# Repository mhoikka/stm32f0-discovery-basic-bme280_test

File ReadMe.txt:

How to use this project:
-Fabricate a PCB using the Gerber and Drill files in the FabricationFiles folder
-Buy all components in the Components/AllComponents.csv file (breakout boards can be used for the NRF24L01+ and BME280 chips if soldering skills and access to a hot air gun are limiting factors. There is no need to solder on any of the components attached to the NRF and BME if the breakout boards are used.)
-Solder on all components according to the KiCAD schematic
-Run raspberry pi code in linked GitHub repo (https://github.com/mhoikka/SPItoNRF.git)
-Insert 2 CR2032 batteries to power on the device
-Collect data and modify code as needed

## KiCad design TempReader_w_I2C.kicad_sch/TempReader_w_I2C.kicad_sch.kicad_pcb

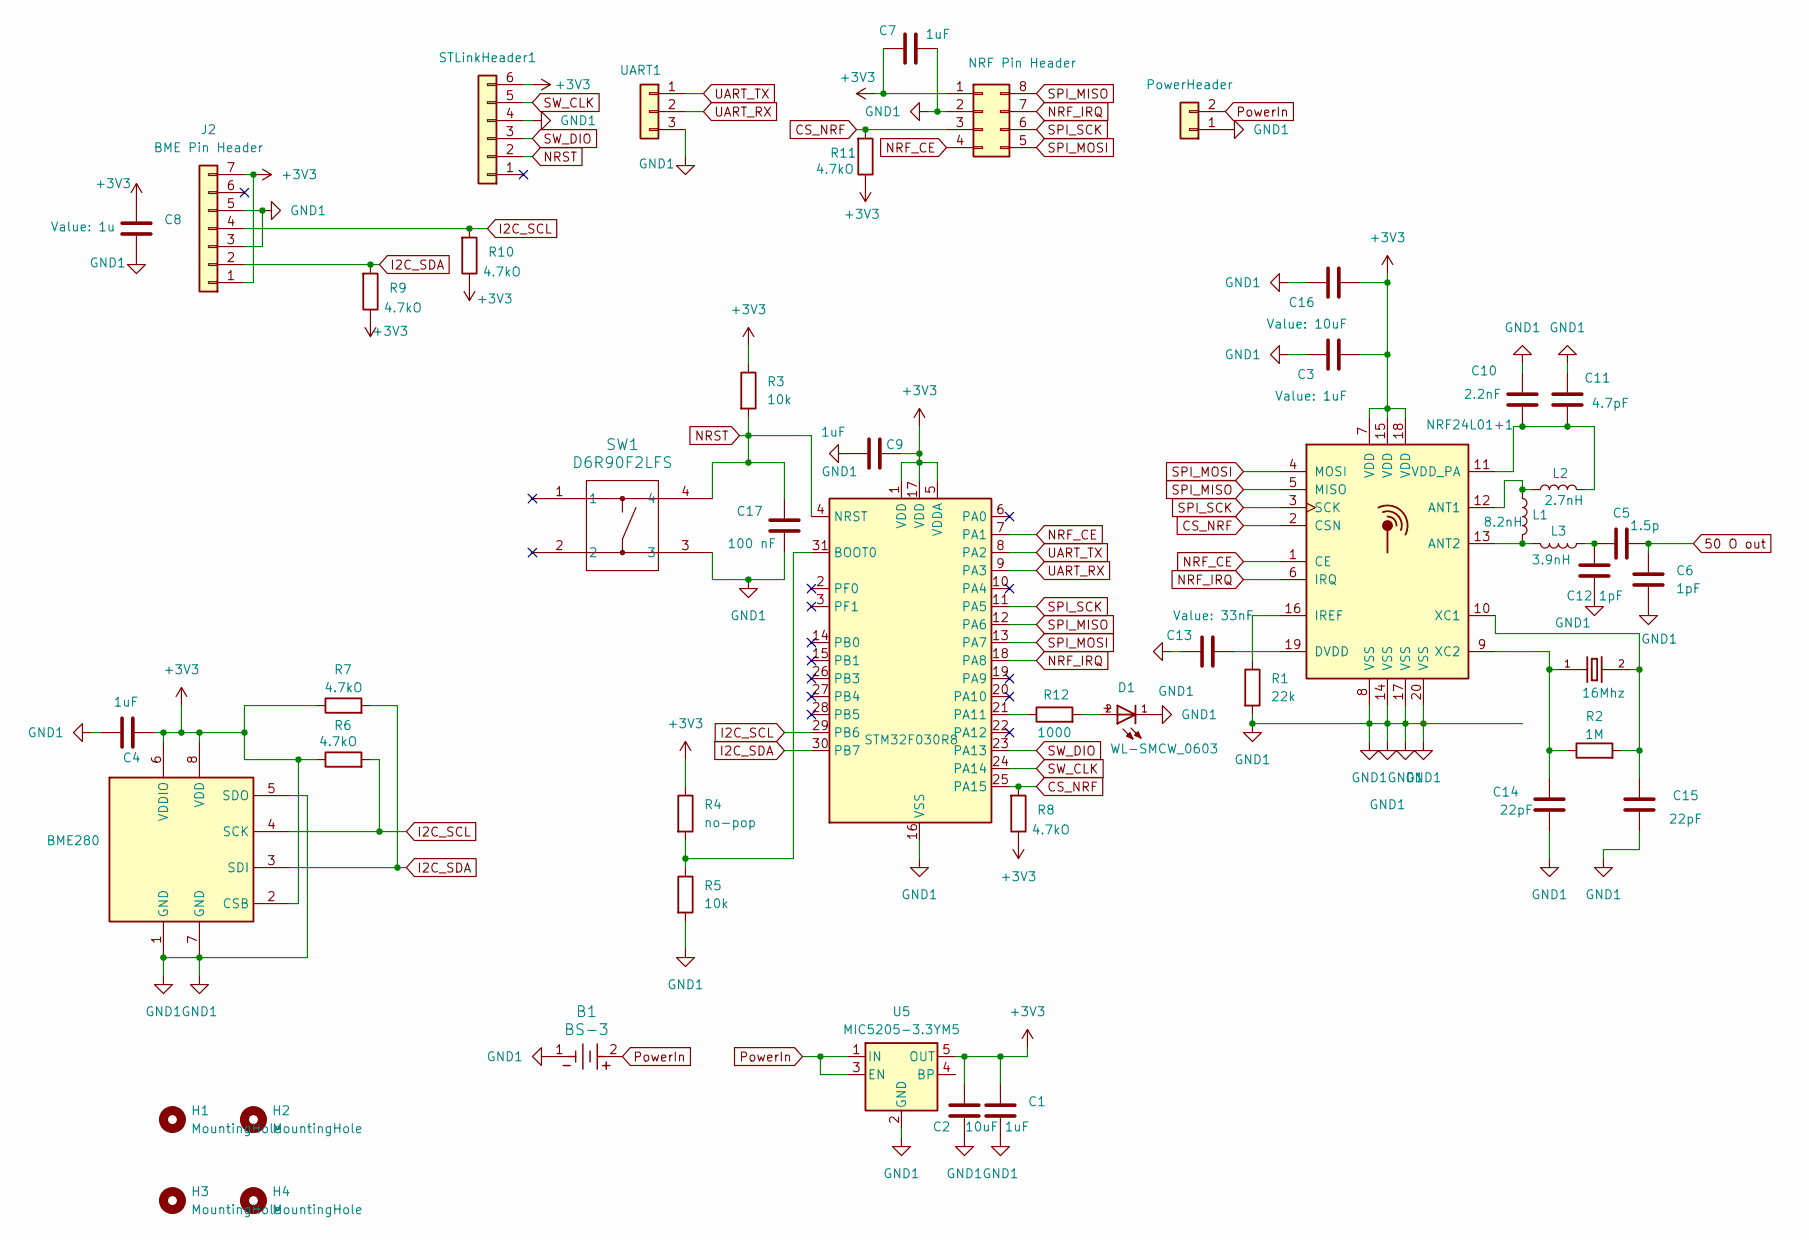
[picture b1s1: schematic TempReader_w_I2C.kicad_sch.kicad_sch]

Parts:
B1: BS-3; BS-3_MPD
BME280: BME280; Bosch_LGA-8_2.5x2.5mm_P0.65mm_ClockwisePinNumbering
C1, C3, C4, C7, C9: 1uF; C_0603_1608Metric_Pad1.08x0.95mm_HandSolder
C2, C16: 10uF; C_0603_1608Metric_Pad1.08x0.95mm_HandSolder
C5: 1.5p; C_0402_1005Metric_Pad0.74x0.62mm_HandSolder
C6, C12: 1pF; C_0402_1005Metric_Pad0.74x0.62mm_HandSolder
C8: 1u; C_0603_1608Metric_Pad1.08x0.95mm_HandSolder
C10: 2.2nF; C_0402_1005Metric_Pad0.74x0.62mm_HandSolder
C11: 4.7pF; C_0402_1005Metric_Pad0.74x0.62mm_HandSolder
C13: 33nF; C_0603_1608Metric_Pad1.08x0.95mm_HandSolder
C14, C15: 22pF; C_0603_1608Metric_Pad1.08x0.95mm_HandSolder
C17: 100 nF; C_0603_1608Metric_Pad1.08x0.95mm_HandSolder
D1: WL-SMCW_0603
H1, H2, H3, H4: MountingHole; MountingHole_2.2mm_M2
J1: NRF Pin Header; CON8_2X4_TU_SSQ
J2: BME Pin Header; PinHeader_1x07_P2.54mm_Vertical
J3: PowerHeader; PinHeader_1x02_P2.54mm_Vertical
L1: 8.2nH; L_0402_1005Metric_Pad0.77x0.64mm_HandSolder
L2: 2.7nH; L_0402_1005Metric_Pad0.77x0.64mm_HandSolder
L3: 3.9nH; L_0402_1005Metric_Pad0.77x0.64mm_HandSolder
NRF24L01+1: QFN-20-1EP_4x4mm_P0.5mm_EP2.5x2.5mm
R1: 22k; R_0603_1608Metric_Pad0.98x0.95mm_HandSolder
R2: 1M; R_0603_1608Metric_Pad0.98x0.95mm_HandSolder
R3, R5: 10k; R_0603_1608Metric_Pad0.98x0.95mm_HandSolder
R4: no-pop; R_0603_1608Metric_Pad0.98x0.95mm_HandSolder
R6, R7, R8, R9, R10, R11: 4.7kO; R_0603_1608Metric_Pad0.98x0.95mm_HandSolder
R12: 1000; R_0603_1608Metric
STLinkHeader1: NOT SURE WHAT THIS IS; PinHeader_1x06_P2.54mm_Vertical
STM32F030R8: LQFP-32_7x7mm_P0.8mm
SW1: D6R90F2LFS; D6R90_CNK
U5: MIC5205-3.3YM5; SOT-23-5
UART1: UART; PinHeader_1x03_P2.54mm_Vertical
Y2: 16Mhz; XTAL_ECS-160-12-4X-GM

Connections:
50 O out: C5.2, C6.1
+3V3: BME280.2 (CSB), BME280.6 (VDDIO), BME280.8 (VDD), C1.1, C2.1, C3.2, C4.1, C7.2, C8.1, C9.1, C16.2, J1.1, J2.1, J2.7, NRF24L01+1.7 (VDD), NRF24L01+1.15 (VDD), NRF24L01+1.18 (VDD), R3.1, R4.1, R6.1, R7.1, R8.1, R9.1, R10.1, R11.1, STLinkHeader1.6, STM32F030R8.1 (VDD), STM32F030R8.5 (VDDA), STM32F030R8.17 (VDD), U5.5 (OUT)
CS_NRF: J1.3, NRF24L01+1.2 (CSN), R8.2, R11.2, STM32F030R8.25 (PA15)
GND1: B1.1, BME280.1 (GND), BME280.5 (SDO), BME280.7 (GND), C1.2, C2.2, C3.1, C4.2, C6.2, C7.1, C8.2, C9.2, C10.1, C11.1, C12.2, C13.1, C14.2, C15.2, C16.1, C17.2, D1.1, J1.2, J2.3, J2.5, J3.1, NRF24L01+1.8 (VSS), NRF24L01+1.14 (VSS), NRF24L01+1.17 (VSS), NRF24L01+1.20 (VSS), R1.2, R5.2, STLinkHeader1.4, STM32F030R8.16 (VSS), STM32F030R8.32 (VSS), SW1.3, U5.2 (GND), UART1.3
I2C_SCL: BME280.4 (SCK), J2.4, R6.2, R10.2, STM32F030R8.29 (PB6)
I2C_SDA: BME280.3 (SDI), J2.2, R7.2, R9.2, STM32F030R8.30 (PB7)
NRF_CE: J1.4, NRF24L01+1.1 (CE), STM32F030R8.7 (PA1)
NRF_IRQ: J1.7, NRF24L01+1.6 (IRQ), STM32F030R8.18 (PA8)
NRST: C17.1, R3.2, STLinkHeader1.2, STM32F030R8.4 (NRST), SW1.4
unnamed: C5.1, C12.1, L3.1
unnamed: D1.2, R12.2
unnamed: L1.1, L2.1, NRF24L01+1.12 (ANT1)
unnamed: L1.2, L3.2, NRF24L01+1.13 (ANT2)
unnamed: C13.2, NRF24L01+1.19 (DVDD)
unnamed: NRF24L01+1.16 (IREF), R1.1
unnamed: C10.2, C11.2, L2.2, NRF24L01+1.11 (VDD_PA)
unnamed: C15.1, NRF24L01+1.10 (XC1), R2.2, Y2.2
unnamed: C14.1, NRF24L01+1.9 (XC2), R2.1, Y2.1
unnamed: R4.2, R5.1, STM32F030R8.31 (BOOT0)
unnamed: R12.1, STM32F030R8.21 (PA11)
PowerIn: B1.2, J3.2, U5.1 (IN), U5.3 (EN)
SPI_MISO: J1.8, NRF24L01+1.5 (MISO), STM32F030R8.12 (PA6)
SPI_MOSI: J1.5, NRF24L01+1.4 (MOSI), STM32F030R8.13 (PA7)
SPI_SCK: J1.6, NRF24L01+1.3 (SCK), STM32F030R8.11 (PA5)
SW_CLK: STLinkHeader1.5, STM32F030R8.24 (PA14)
SW_DIO: STLinkHeader1.3, STM32F030R8.23 (PA13)
UART_RX: STM32F030R8.9 (PA3), UART1.2
UART_TX: STM32F030R8.8 (PA2), UART1.1

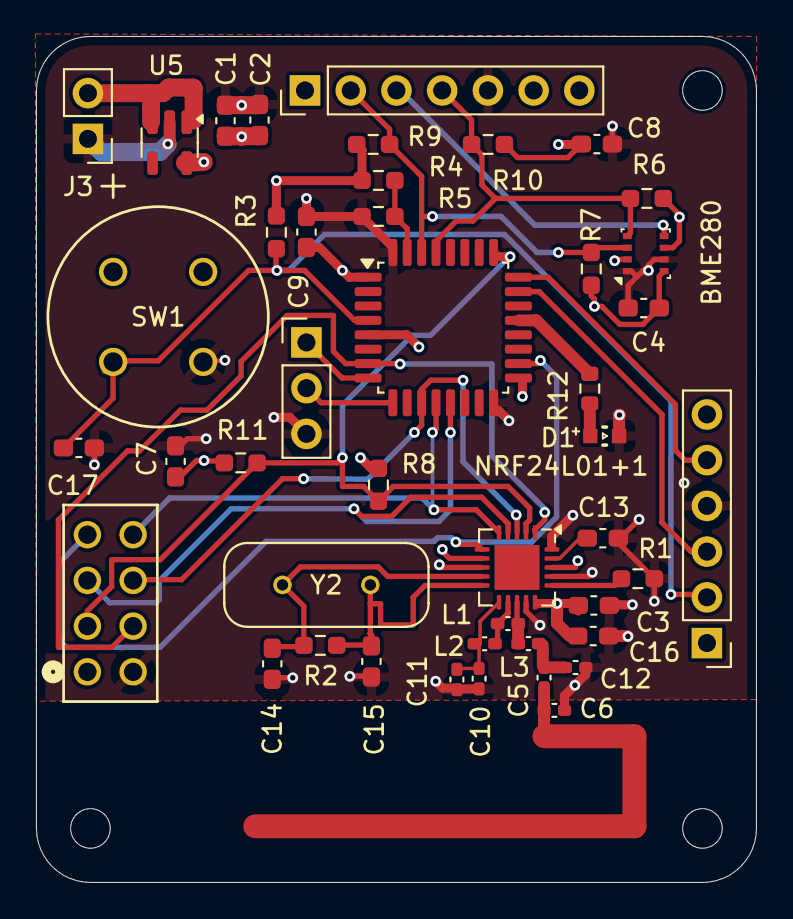
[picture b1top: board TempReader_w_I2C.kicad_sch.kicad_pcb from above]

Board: 4 copper layers, 40.0 x 47.0 mm, 47 parts (0 on the bottom side), 28 nets.

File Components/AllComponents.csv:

"Reference","Value","Datasheet","Footprint","Qty","DNP"
"B1","BS-3","BS-3","footprints:BS-3_MPD","1",""
"BME280","BME280","https://www.bosch-sensortec.com/media/boschsensortec/downloa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","Package_LGA:Bosch_LGA-8_2.5x2.5mm_P0.65mm_ClockwisePinNumbering","1",""
"C1,C3,C4,C7,C9","1uF","~","Capacitor_SMD:C_0603_1608Metric_Pad1.08x0.95mm_HandSolder","5",""
"C2,C16","10uF","~","Capacitor_SMD:C_0603_1608Metric_Pad1.08x0.95mm_HandSolder","2",""
"C5","1.5p","~","Capacitor_SMD:C_0402_1005Metric_Pad0.74x0.62mm_HandSolder","1",""
"C6,C12","1pF","~","Capacitor_SMD:C_0402_1005Metric_Pad0.74x0.62mm_HandSolder","2",""
"C8","1u","~","Capacitor_SMD:C_0603_1608Metric_Pad1.08x0.95mm_HandSolder","1",""
"C10","2.2nF","~","Capacitor_SMD:C_0402_1005Metric_Pad0.74x0.62mm_HandSolder","1",""
"C11","4.7pF","~","Capacitor_SMD:C_0402_1005Metric_Pad0.74x0.62mm_HandSolder","1",""
"C13","33nF","~","Capacitor_SMD:C_0603_1608Metric_Pad1.08x0.95mm_HandSolder","1",""
"C14,C15","22pF","~","Capacitor_SMD:C_0603_1608Metric_Pad1.08x0.95mm_HandSolder","2",""
"C17","100 nF","~","Capacitor_SMD:C_0603_1608Metric_Pad1.08x0.95mm_HandSolder","1",""
"D1","WL-SMCW_0603","","footprints:WL-SMCW_0603","1",""
"J1","NRF Pin Header","~","footprints:CON8_2X4_TU_SSQ","1",""
"J2","BME Pin Header","~","Connector_PinHeader_2.54mm:PinHeader_1x07_P2.54mm_Vertical","1",""
"J3","PowerHeader","~","Connector_PinHeader_2.54mm:PinHeader_1x02_P2.54mm_Vertical","1",""
"L1","8.2nH","~","Inductor_SMD:L_0402_1005Metric_Pad0.77x0.64mm_HandSolder","1",""
"L2","2.7nH","~","Inductor_SMD:L_0402_1005Metric_Pad0.77x0.64mm_HandSolder","1",""
"L3","3.9nH","~","Inductor_SMD:L_0402_1005Metric_Pad0.77x0.64mm_HandSolder","1",""
"NRF24L01+1,STM32F030R8","~","-- mixed values --","-- mixed values --","2",""
"R1","22k","~","Resistor_SMD:R_0603_1608Metric_Pad0.98x0.95mm_HandSolder","1",""
"R2","1M","~","Resistor_SMD:R_0603_1608Metric_Pad0.98x0.95mm_HandSolder","1",""
"R3,R5","10k","~","Resistor_SMD:R_0603_1608Metric_Pad0.98x0.95mm_HandSolder","2",""
"R4","no-pop","~","Resistor_SMD:R_0603_1608Metric_Pad0.98x0.95mm_HandSolder","1",""
"R6,R7,R8,R9,R10,R11","4.7kO","~","Resistor_SMD:R_0603_1608Metric_Pad0.98x0.95mm_HandSolder","6",""
"R12","1000","~","Resistor_SMD:R_0603_1608Metric","1",""
"STLinkHeader1","NOT SURE WHAT THIS IS","~","Connector_PinHeader_2.54mm:PinHeader_1x06_P2.54mm_Vertical","1",""
"SW1","D6R90F2LFS","D6R90F2LFS","D6R90_CNK","1",""
"U5","MIC5205-3.3YM5","http://ww1.microchip.com/downloads/en/DeviceDoc/20005785A.pdf","Package_TO_SOT_SMD:SOT-23-5","1",""
"UART1","UART","~","Connector_PinHeader_2.54mm:PinHeader_1x03_P2.54mm_Vertical","1",""
"Y2","16Mhz","","ECS-160-12-4X-GM:XTAL_ECS-160-12-4X-GM","1",""

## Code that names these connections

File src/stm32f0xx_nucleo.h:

/**
  ******************************************************************************
  * @file    stm32f0xx_nucleo.h
  * @author  MCD Application Team
  * @version V1.0.0
  * @date    11-February-2014
  * @brief   This file contains all the functions prototypes for the
  *          stm32f0xx_nucleo.c driver.
  ******************************************************************************
  * @attention
  *
  * <h2><center>&copy; COPYRIGHT 2014 STMicroelectronics</center></h2>
  *
  * Licensed under MCD-ST Liberty SW License Agreement V2, (the "License");
  * You may not use this file except in compliance with the License.
  * You may obtain a copy of the License at:
  *
  *        http://www.st.com/software_license_agreement_liberty_v2
  *
  * Unless required by applicable law or agreed to in writing, software 
  * distributed under the License is distributed on an "AS IS" BASIS, 
  * WITHOUT WARRANTIES OR CONDITIONS OF ANY KIND, either express or implied.
  * See the License for the specific language governing permissions and
  * limitations under the License.
  *
  ******************************************************************************
  */

/* Define to prevent recursive inclusion -------------------------------------*/
#ifndef __STM32F0XX_NUCLEO_H
#define __STM32F0XX_NUCLEO_H

#ifdef __cplusplus
 extern "C" {
#endif
                                              
/* Includes ------------------------------------------------------------------*/
#include "stm32f0xx.h"
#include "stm32f0xx_adc.h"

/** @addtogroup Utilities
  * @{
  */ 

/** @addtogroup STM32F0XX_NUCLEO
  * @{
  */
      
/** @defgroup STM32F0XX_NUCLEO_LOW_LEVEL 
  * @brief This file provides set of firmware functions to manage Leds and push-button
  *        available on STM32NUCLEO Kit from STMicroelectronics.
  * @{
  */

/** @defgroup STM32F0XX_NUCLEO_LOW_LEVEL_Exported_Types
  * @{
  */
typedef enum 
{
  LED2 = 0,
  
} Led_TypeDef;

typedef enum 
{  
  BUTTON_USER = 0,
} Button_TypeDef;

typedef enum 
{  
  BUTTON_MODE_GPIO = 0,
  BUTTON_MODE_EXTI = 1
} ButtonMode_TypeDef; 

/* The Joystick is available on adafruit 1.8" TFT shield */     
typedef enum 
{ 
  JOY_NONE = 0,
  JOY_SEL = 1,
  JOY_DOWN = 2,
  JOY_LEFT = 3,
  JOY_RIGHT = 4,
  JOY_UP = 5
} JOYState_TypeDef;

/**
  * @}
  */

/** @defgroup STM32F0XX_NUCLEO_LOW_LEVEL_Exported_Macros
  * @{
  */
/**
  * @brief LCD control lines (CS and DC) management
  */
#define LCD_CS_HIGH() LCD_CS_GPIO_PORT->BSRR = LCD_CS_PIN
#define LCD_CS_LOW()  LCD_CS_GPIO_PORT->BRR = LCD_CS_PIN
#define LCD_DC_HIGH() LCD_DC_GPIO_PORT->BSRR = LCD_DC_PIN
#define LCD_DC_LOW()  LCD_DC_GPIO_PORT->BRR = LCD_DC_PIN

/**
  * @brief SD CS line management 
  */
#define SD_CS_HIGH()  SD_CS_GPIO_PORT->BSRR = SD_CS_PIN
#define SD_CS_LOW()   SD_CS_GPIO_PORT->BRR = SD_CS_PIN    

/**
  * @}
  */  

/** @defgroup STM32F0xx_NUCLEO_LOW_LEVEL_Exported_Constants
  * @{
  */ 
/** @addtogroup STM32F0xx_NUCLEO_LOW_LEVEL_LED
  * @{
  */
#define LEDn                             1

#define LED2_PIN                         GPIO_Pin_5
#define LED2_GPIO_PORT                   GPIOA
#define LED2_GPIO_CLK                    RCC_AHBPeriph_GPIOA  

/**
  * @}
  */ 
/** @addtogroup STM32F0xx_NUCLEO_LOW_LEVEL_BUTTON
  * @{
  */  
#define BUTTONn                          1  

/**
 * @brief Wakeup push-button
 */
#define USER_BUTTON_PIN                GPIO_Pin_13
#define USER_BUTTON_GPIO_PORT          GPIOC
#define USER_BUTTON_GPIO_CLK           RCC_AHBPeriph_GPIOC
#define USER_BUTTON_EXTI_LINE          EXTI_Line13
#define USER_BUTTON_EXTI_PORT_SOURCE   EXTI_PortSourceGPIOC
#define USER_BUTTON_EXTI_PIN_SOURCE    EXTI_PinSource13
#define USER_BUTTON_EXTI_IRQn          EXTI4_15_IRQn 
/**
  * @}
  */
    
/** @addtogroup STM32F0XX_NUCLEO_LOW_LEVEL_SPI
  * @{
  */
/**
  * @brief  SPI Interface pins
  */
/* The LCD and uSD card are available on adafruit 1.8" TFT shield */
#define LCD_SD_SPI                    SPI1
#define LCD_SD_SPI_CLK                RCC_APB2Periph_SPI1

#define SPI_SCK_PIN                   GPIO_Pin_5                  /* PA.05 */
#define SPI_SCK_GPIO_PORT             GPIOA                       /* GPIOA */
#define SPI_SCK_GPIO_CLK              RCC_AHBPeriph_GPIOA
#define SPI_SCK_SOURCE                GPIO_PinSource5
#define SPI_SCK_AF                    GPIO_AF_0

#define SPI_MISO_PIN                  GPIO_Pin_6                  /* PA.06 */
#define SPI_MISO_GPIO_PORT            GPIOA                       /* GPIOA */
#define SPI_MISO_GPIO_CLK             RCC_AHBPeriph_GPIOA
#define SPI_MISO_SOURCE               GPIO_PinSource6
#define SPI_MISO_AF                   GPIO_AF_0

#define SPI_MOSI_PIN                  GPIO_Pin_7                  /* PA.07 */
#define SPI_MOSI_GPIO_PORT            GPIOA                       /* GPIOA */
#define SPI_MOSI_GPIO_CLK             RCC_AHBPeriph_GPIOA
#define SPI_MOSI_SOURCE               GPIO_PinSource7
#define SPI_MOSI_AF                   GPIO_AF_0
/**
  * @}
  */  
    
/**
  * @brief  SD Chip Select pin
  */
#define SD_CS_PIN                     GPIO_Pin_5                  /* PB.5 */
#define SD_CS_GPIO_PORT               GPIOB                       /* GPIOB */
#define SD_CS_GPIO_CLK                RCC_AHBPeriph_GPIOB

/**
  * @brief  LCD Data/Command pin
  */
#define LCD_DC_PIN                    GPIO_Pin_9                  /* PA.9 */
#define LCD_DC_GPIO_PORT              GPIOA                       /* GPIOA */
#define LCD_DC_GPIO_CLK               RCC_AHBPeriph_GPIOA

/**
  * @brief  LCD Chip Select pin
  */
#define LCD_CS_PIN                    GPIO_Pin_6                  /* PB.6*/
#define LCD_CS_GPIO_PORT              GPIOB                       /* GPIOB */
#define LCD_CS_GPIO_CLK               RCC_AHBPeriph_GPIOB
     
/**
  * @brief  ADC Interface pins
  */
/* The ADC is used to detect motion of Joystick available on adafruit 1.8" TFT shield */   
#define ADCx                            ADC1
#define ADC_CLK                         RCC_APB2Periph_ADC1
    
#define ADC_GPIO_PIN                    GPIO_Pin_0                  /* PB.0  */
#define ADC_GPIO_PORT                   GPIOB                       /* GPIOB */
#define ADC_GPIO_CLK                    RCC_AHBPeriph_GPIOB
/**
  * @}
  */

/** @defgroup STM32F0XX_NUCLEO_LOW_LEVEL_Exported_Functions
  * @{
  */
void STM_EVAL_LEDInit(Led_TypeDef Led);
void STM_EVAL_LEDOn(Led_TypeDef Led);
void STM_EVAL_LEDOff(Led_TypeDef Led);
void STM_EVAL_LEDToggle(Led_TypeDef Led);
void STM_EVAL_PBInit(Button_TypeDef Button, ButtonMode_TypeDef Button_Mode);
uint32_t STM_EVAL_PBGetState(Button_TypeDef Button);

/* Functions to configure and manage the STM32F0xx resources (SPI and ADC) used to drive 
   LCD, uSD card and Joystick available in adafruit 1.8" TFT shield */
void STM_SPI_Init(void);
uint8_t STM_SPI_WriteRead(uint8_t Data);
void LCD_CtrlLines_Config(void);
void SD_CtrlLines_Config(void);
void STM_ADC_Config(void);
JOYState_TypeDef STM_Get_JOYState(void);

/**
  * @}
  */

#ifdef __cplusplus
}
#endif

#endif /* __STM32F0XX_NUCLEO_H */
/**
  * @}
  */ 

/**
  * @}
  */ 

/**
  * @}
  */ 

/************************ (C) COPYRIGHT STMicroelectronics *****END OF FILE****/

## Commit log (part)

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2024-10-06 SPI test was not in fact working
2024-10-08 Please tell me this was not the issue
2024-10-08 This was probably the issue
2024-10-08 Try adding a delay
2024-10-08 Try adding a delay for powerup
2024-10-08 Wait for powerup to read
2024-10-09 New read/write SPI function
2024-10-10 Cleaning up code
2024-10-19 KiCAD files
2024-10-25 Added test code to transmit one byte of data
2024-10-25 Moved variable declarations
2024-10-25 Added debug lines
2024-10-26 Removed debug lines
2024-10-26 Fix array copy
2024-10-26 Fix array copy the sequel
2024-10-26 Add code to flush TX FIFO
2024-10-26 Add code to clear MAX_RT bit
2024-10-26 See if data is being transmitted by disabling AUTOACK
2024-10-26 Data is being transmitted
2024-10-26 Clear transmit data bit
2024-10-26 Fix transmission rate
2024-10-26 Works :)
2024-10-26 what
2024-10-26 Data = 3
2024-10-26 Test if sending
2024-10-26 It is sending
2024-10-26 Clear all IRQ
2024-10-27 test
2024-10-31 NO ack testing
2024-10-31 Fix ternary operator
2024-10-31 Check if CE is the problem
2024-10-31 Check if auto ack is the problem
2024-10-31 Check if RX payload size is the issue
2024-10-31 Pull CE pin down
2024-11-08 Set payload length
2024-11-10 Cycle sending noack payload
2024-11-10 revert
2024-11-10 set payload size
2024-11-10 speed up retrannsmission
2024-11-10 longer transmissions
2024-11-10 Fix type issue
2024-11-10 Register access issue
2024-11-10 Remove unecessary autoack
2024-11-10 Add auto_ack
2024-11-10 Remove auto_ack
2024-11-11 Transmit multiple bytes
2024-11-11 Transmit more than 32 bytes
2024-11-16 Add ACK functionality
2024-11-16 Debug adding ack functionality
2024-11-16 Test BME with NRF attached
2024-11-16 Test sending BME280 data over NRF
2024-11-16 Debugging
2024-12-01 Trying to send BME data with battery power
2024-12-01 Reformatting BME280 data into int
2024-12-03 Preventing reset cycle
2024-12-03 Preventing reset cycle for BME280
2024-12-03 Issue hopefully fixed with BME reset cycle
2024-12-03 BME setup reordering
2024-12-03 Check I2C for BME address
2024-12-03 Use BME Init function
2024-12-03 Try reading chip id
2024-12-03 added debug prints
2024-12-03 check registers manually
2024-12-03 Fix function definition
2024-12-03 Use different read function
2024-12-03 Try built in
2024-12-03 Add device id for bme280
2024-12-03 typo
2024-12-03 Debugg prints
2024-12-03 Remove waits for I2C busy
2024-12-03 Get back to a working state
2024-12-19 Add power save functionality
2024-12-20 Add power save functionality for BME 280
2024-12-20 Test if normal mode solves pressure bug
2024-12-20 Switch back to forced mode and add delay
2024-12-20 Print SysTick tick rate
2024-12-20 Debug SysTick tick rate
2024-12-20 Test string print
2024-12-20 Change initialization order
2024-12-20 Add sleep mode for STM32
2024-12-20 Cast float to int for SysTick
2024-12-20 Change Delay timing
2024-12-20 Don't disable systick
2024-12-20 Enable SysTick interrupt
2024-12-20 Reorder delay function
2024-12-20 Use NVIC to set priority for SysTick
2024-12-20 Remove delay timer
2024-12-20 Remove sleep changes
2024-12-20 Test if config is successful
2024-12-20 Bug fix
2024-12-20 Source the timing issue
2024-12-20 Try using RTC
2024-12-20 Use SysTick loop to wake up chip
2024-12-21 Use RTC alarm to wake up STM32
2024-12-21 Include code from rtc
2024-12-21 Struct not necessary
2024-12-21 Enable LSE
2024-12-21 Enable LSI
2024-12-21 Debug print
2024-12-21 Debug prints
2024-12-21 Give alarm an interrupt
2024-12-21 NVIC config
2024-12-21 Debug
2024-12-21 Move code
2024-12-21 add EXT1 setup
2024-12-21 Change alarm priority to 3
2024-12-21 Remove interrupt mask
2024-12-21 Add debug prints for alarm
2024-12-21 Increase interrupt priority
2024-12-21 Add header files
2024-12-21 Interrupt handler function
2024-12-21 Interrupt handler function remove second
2024-12-21 Check if alarm is set correctly
2024-12-21 Print debug
2024-12-21 Enable writing to Calendar
2024-12-21 Enablr EXT1 for interrupts
2024-12-24 Disable sleep mode for now
2024-12-25 Test changes for programming using STLink
2024-12-26 Added debug prints for UART
2024-12-27 Slightly change comments
2024-12-28 Warning fixes
2024-12-28 Warning error fixes
2024-12-28 All warnings gone hopefully
2024-12-28 Test version for flash
2024-12-28 Remove functionality to test UART
2024-12-28 Change UART settings
2024-12-28 Typo in UART settings
2024-12-28 Change more UART settings
2024-12-28 Reenable system clock
2024-12-28 Change UART pins again
2024-12-29 change delay function
2024-12-29 Fix proj file
2024-12-29 Update Makefile
2024-12-30 Changed RAM settings in config
2024-12-30 Nucleo branch created
2025-01-01 Change data rate and signal strength
2025-01-01 Add GDB debug option
2025-01-02 Test higher transmit speed
2025-01-02 Correct address for pipe 1
2025-05-12 Update main.c
    Removed commented code
2025-05-12 Update Peripheral_Init.c
    Delete commented code and TODOs
